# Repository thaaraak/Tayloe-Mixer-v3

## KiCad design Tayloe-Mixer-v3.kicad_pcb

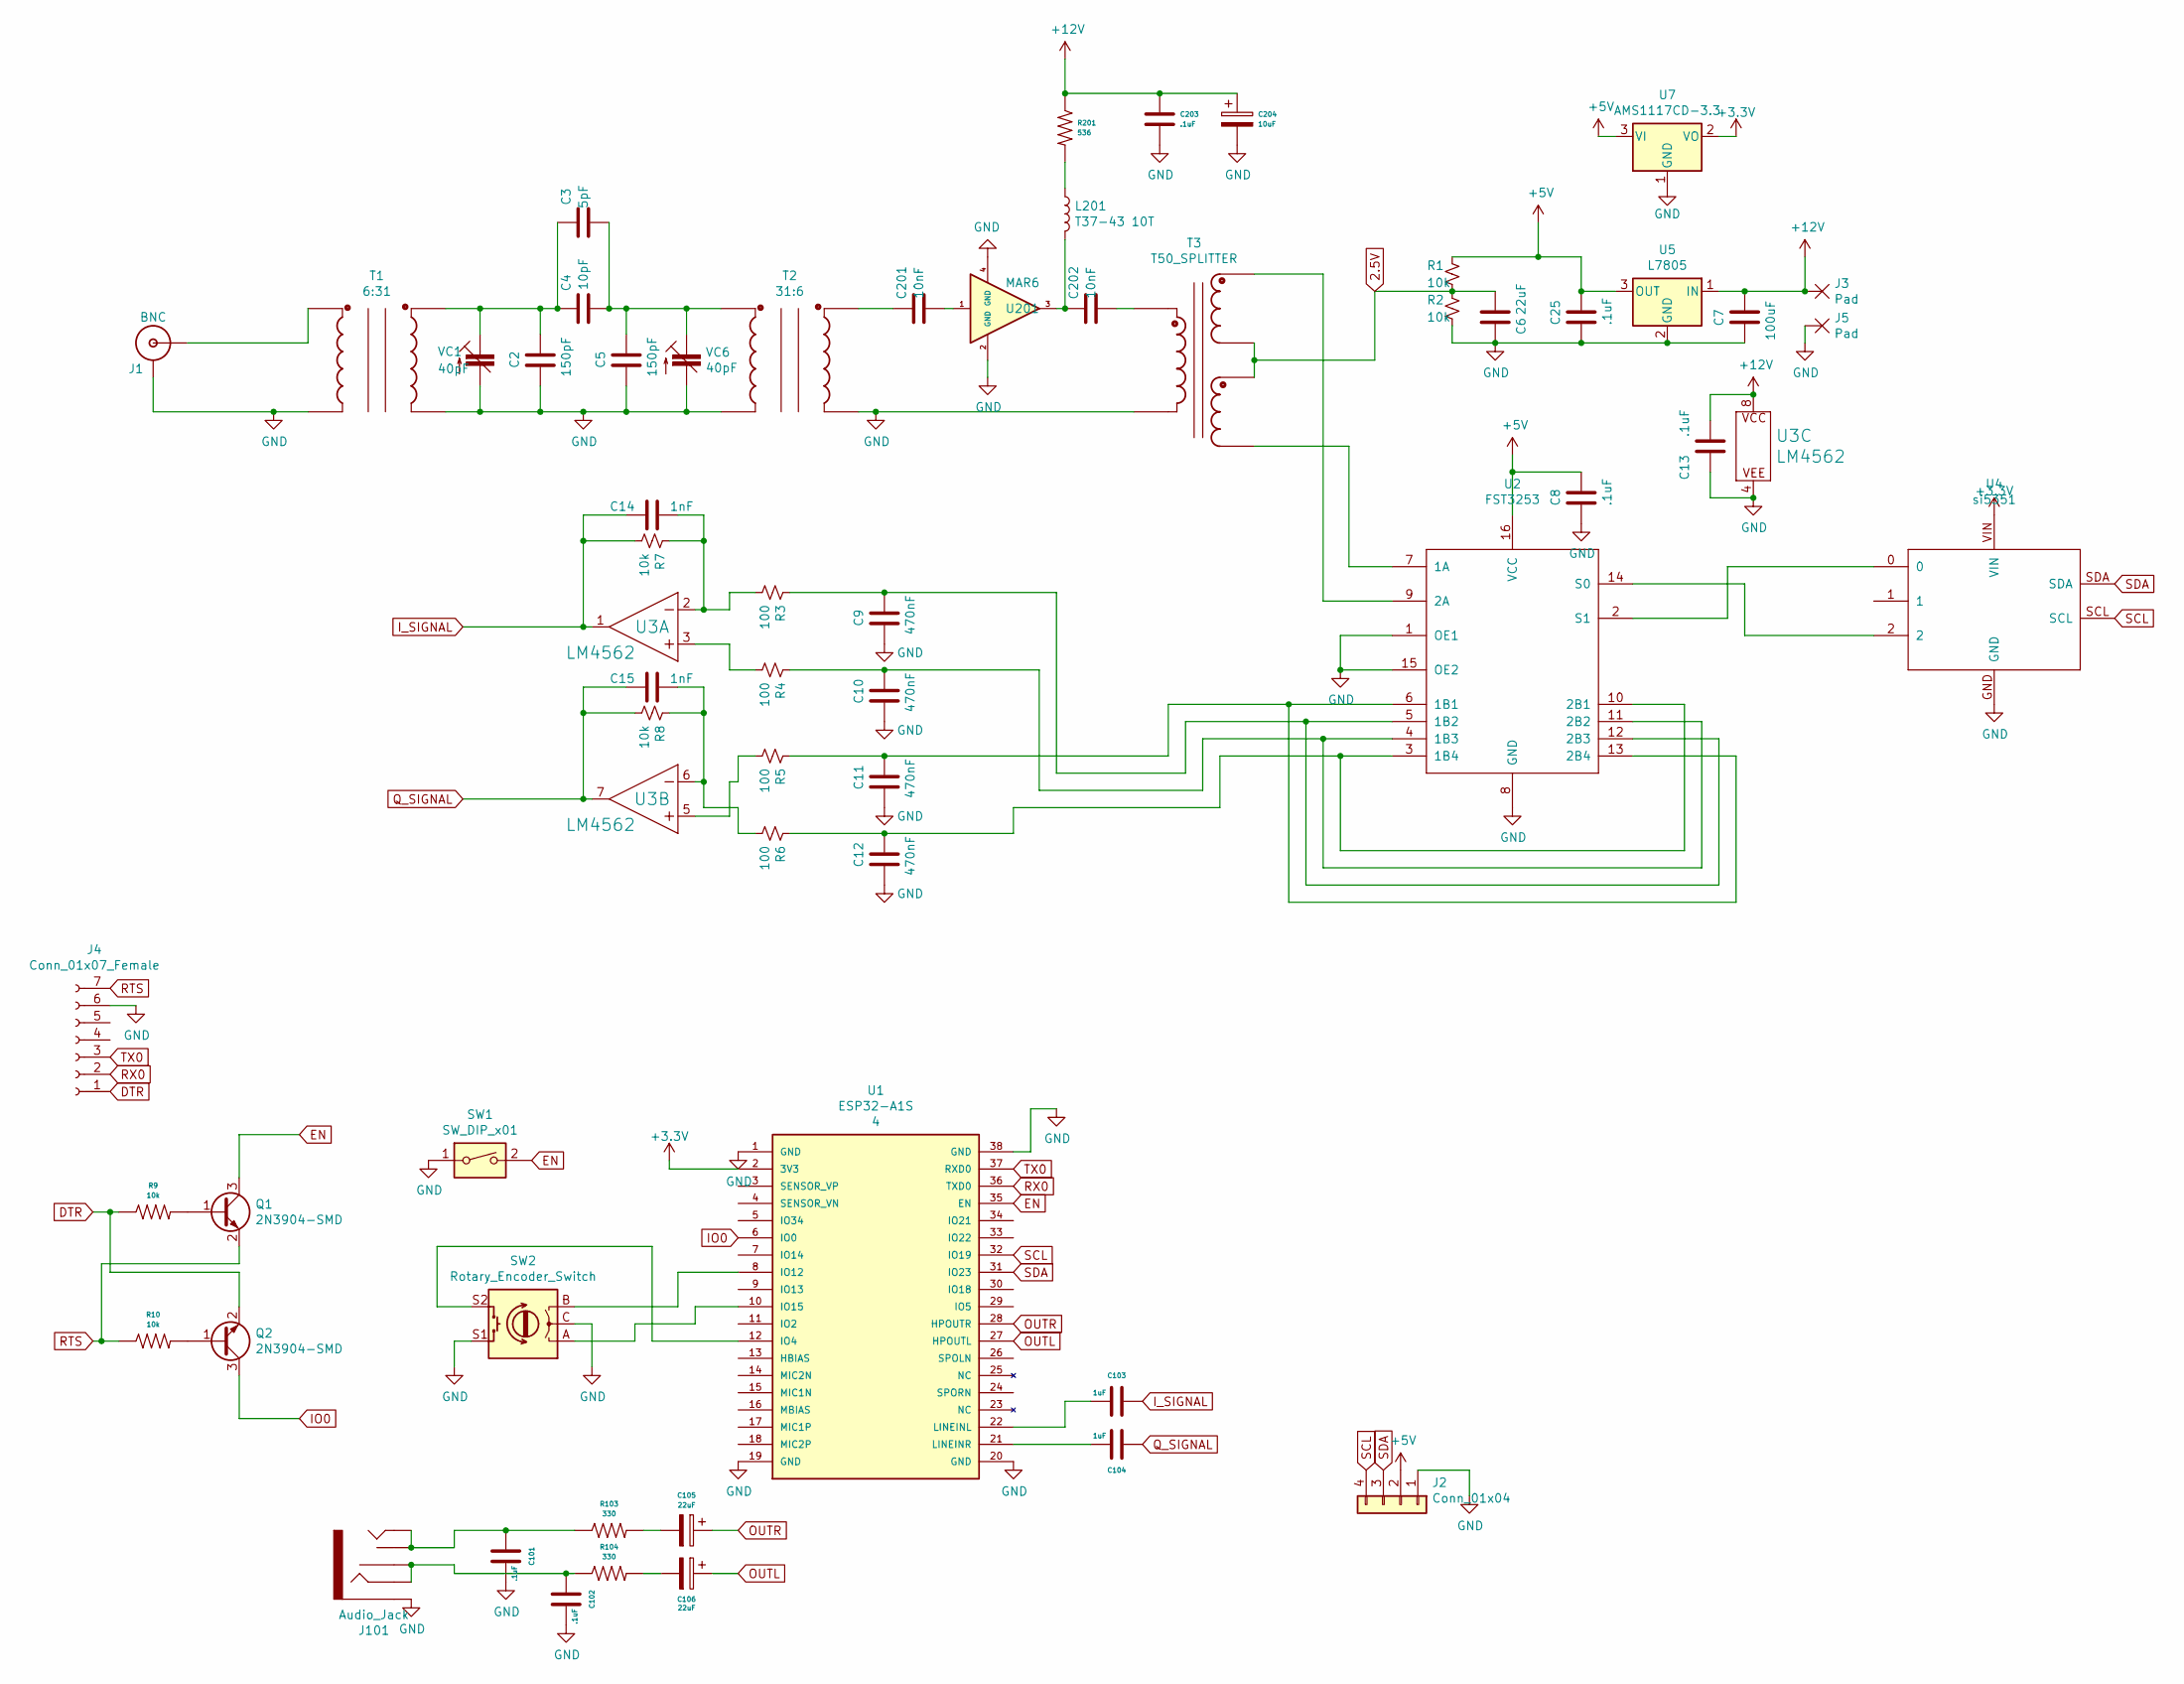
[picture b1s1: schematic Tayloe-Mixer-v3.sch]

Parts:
C2, C5: 150pF; Capacitor 1206
C3: 5pF; Capacitor 1206
C4: 10pF; Capacitor 1206
C6: 22uF; CP_Elec_4x5.4
C7: 100uF; CP_Elec_6.3x5.4
C8, C13, C25, C101, C102, C203: .1uF; Capacitor 1206
C9, C10, C11, C12: 470nF; Capacitor 0805
C14, C15: 1nF; Capacitor 0805
C103, C104: 1uF; Capacitor 1206
C105, C106: 22uF; Cap_4x5.4
C201, C202: 10nF; Capacitor 1206
C204: 10uF; Cap_4x5.4
J1: BNC
J2: Conn_01x04; PinSocket_1x04_P2.54mm_Vertical
J3, J5: Pad
J4: Conn_01x07_Female; PinSocket_1x07_P2.54mm_Vertical
J101: Audio_Jack
L201: T37-43 10T; T37_Inductor
Q1, Q2: 2N3904-SMD; SOT-23
R1, R2, R7, R8, R9, R10: 10k; Resistor 0805
R3, R4, R5, R6: 100; Resistor 0805
R103, R104: 330; Resistor 0805
R201: 536; Resistor 1206
SW1: SW_DIP_x01; SW_PUSH_6mm
SW2: Rotary_Encoder_Switch; RotaryEncoder_Alps_EC11E-Switch_Vertical_H20mm
T1: 6:31; T37 Transformer
T2: 31:6; T37 Transformer
T3: T50_SPLITTER; T50 Trifilar
U1: ESP32-A1S; PARTREV 4
U2: FST3253; SO16
U3: LM4562; SOIC8
U4: si5351
U5: L7805; TO-252-3_TabPin2
U7: AMS1117CD-3.3; SOT-223-3_TabPin2
U201: MAR6; VV105
VC1, VC6: 40pF; trimcap

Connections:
2.5V: C6.1, R1.2, R2.1, T3.C2A, T3.C3B
+3V3: U1.2 (3V3), U4.VIN, U7.2 (VO)
+5V: C8.2, C25.2, J2.2, R1.1, U2.16 (VCC), U5.3 (OUT), U7.3 (VI)
+12V: C7.1, C13.2, C203.1, C204.1, J3.1, R201.1, U3.8 (P$V+), U5.1 (IN)
DTR: J4.1, Q2.2 (E), R9.1
EN: Q1.3 (C), SW1.2, U1.35 (EN)
GND: C2.1, C5.1, C6.2, C7.2, C8.1, C9.1, C10.1, C11.1, C12.1, C13.1, C25.1, C101.2, C102.2, C203.2, C204.2, J1.GND, J2.1, J4.6, J5.1, J101.SLEEVE, R2.2, SW1.1, SW2.C, SW2.S1, T1.C1A, T1.C2A, T2.C1A, T2.C2A, T3.C1A, U1.1 (GND), U1.19 (GND), U1.20 (GND), U1.38 (GND), U2.1 (OE1), U2.8 (GND), U2.15 (OE2), U3.4 (P$V-), U4.GND, U5.2 (GND), U7.1 (GND), U201.2 (GND), U201.4 (GND), VC1.2 (A), VC6.2 (A)
IO0: Q2.3 (C), U1.6 (IO0)
I_SIGNAL: C14.1, C103.1, R7.2, U3.1 (OUT)
unnamed: C2.2, C3.1, C4.1, T1.C2B, VC1.1 (E)
unnamed: C3.2, C4.2, C5.2, T2.C1B, VC6.1 (E)
unnamed: C9.2, R3.1, U2.5 (1B2), U2.12 (2B3)
unnamed: C10.2, R4.1, U2.4 (1B3), U2.11 (2B2)
unnamed: C11.2, R5.1, U2.6 (1B1), U2.13 (2B4)
unnamed: C12.2, R6.1, U2.3 (1B4), U2.10 (2B1)
unnamed: C14.2, R3.2, R7.1, U3.2 (-IN)
unnamed: C15.2, R6.2, R8.1, U3.6 (-IN)
unnamed: C101.1, J101.TIP, J101.TSH, R103.1
unnamed: C102.1, J101.RING, J101.RSH, R104.1
unnamed: C103.2, U1.22 (LINEINL)
unnamed: C104.2, U1.21 (LINEINR)
unnamed: C105.2, R103.2
unnamed: C106.2, R104.2
unnamed: C201.1, T2.C2B
unnamed: C201.2, U201.1
unnamed: C202.1, L201.2, U201.3
unnamed: C202.2, T3.C1B
unnamed: J1.S (OUT), T1.C1B
unnamed: L201.1, R201.2
unnamed: Q1.1 (B), R9.2
unnamed: Q2.1 (B), R10.2
unnamed: R4.2, U3.3 (+IN)
unnamed: R5.2, U3.5 (+IN)
unnamed: SW2.A, U1.10 (IO15)
unnamed: SW2.B, U1.8 (IO12)
unnamed: SW2.S2, U1.12 (IO4)
unnamed: T3.C2B, U2.9 (2A)
unnamed: T3.C3A, U2.7 (1A)
unnamed: U2.2 (S1), U4.0
unnamed: U2.14 (S0), U4.2
OUTL: C106.1, U1.27 (HPOUTL)
OUTR: C105.1, U1.28 (HPOUTR)
Q_SIGNAL: C15.1, C104.1, R8.2, U3.7 (OUT)
RTS: J4.7, Q1.2 (E), R10.1
RX0: J4.2, U1.36 (TXD0)
SCL: J2.4, U1.32 (IO19), U4.SCL
SDA: J2.3, U1.31 (IO23), U4.SDA
TX0: J4.3, U1.37 (RXD0)

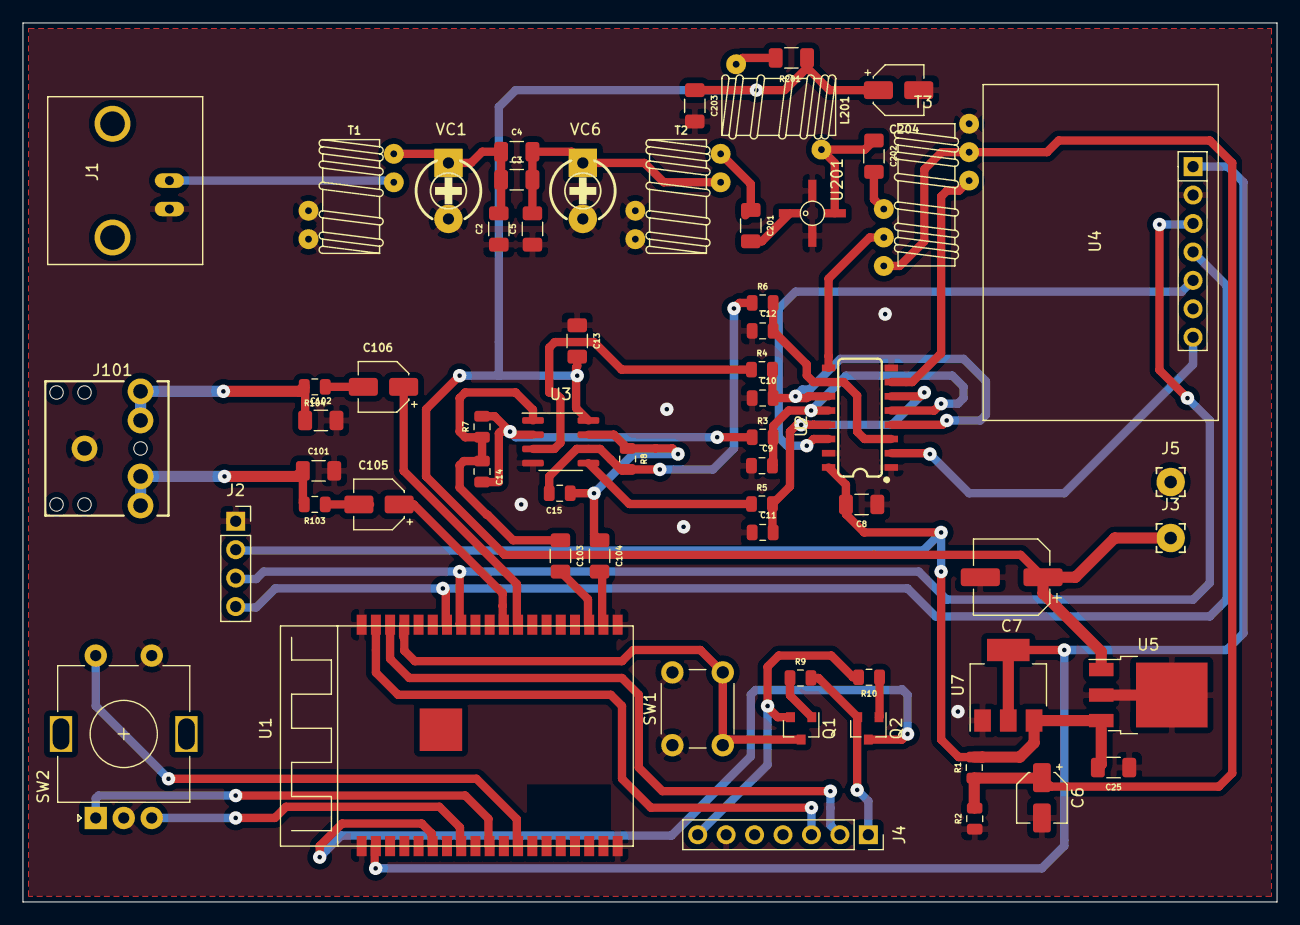
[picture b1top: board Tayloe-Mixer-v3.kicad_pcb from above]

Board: 2 copper layers, 112.0 x 78.5 mm, 61 parts (0 on the bottom side), 48 nets.

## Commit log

2022-10-03 added esp32
2022-10-03 annotate
2022-10-03 finished footprints
2022-10-03 updated pcb
2022-10-03 continue
2022-10-16 board
2022-10-17 updating pcb
2022-10-18 rerouting
2022-10-18 finished?
2022-10-18 fixed audio jack
2022-10-18 added gerber
2022-10-21 fixed rx/tx
2022-10-24 added keepout area under esp32
2022-10-27 moved bpf
